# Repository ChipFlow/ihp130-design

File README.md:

# GF130 Test Chip Repo

## VS Code debugger

* Download the [latest VSIX package](https://github.com/ChipFlow/rtl-debugger/releases/tag/latest) for the extension.
* Install it (eg `code --install-extension ../rtl-debugger-0.0.0.vsix` or right-click in explorer pane and select "Install VSIX").
* `Shift+Ctrl+P` "RTL Debugger: Start Session"
* `Shift+Ctrl+P` "RTL Debugger: Run Simulation Until..." "10ms"
* `Shift+Ctrl+P` "RTL Debugger: Go to Time..." "10ms"

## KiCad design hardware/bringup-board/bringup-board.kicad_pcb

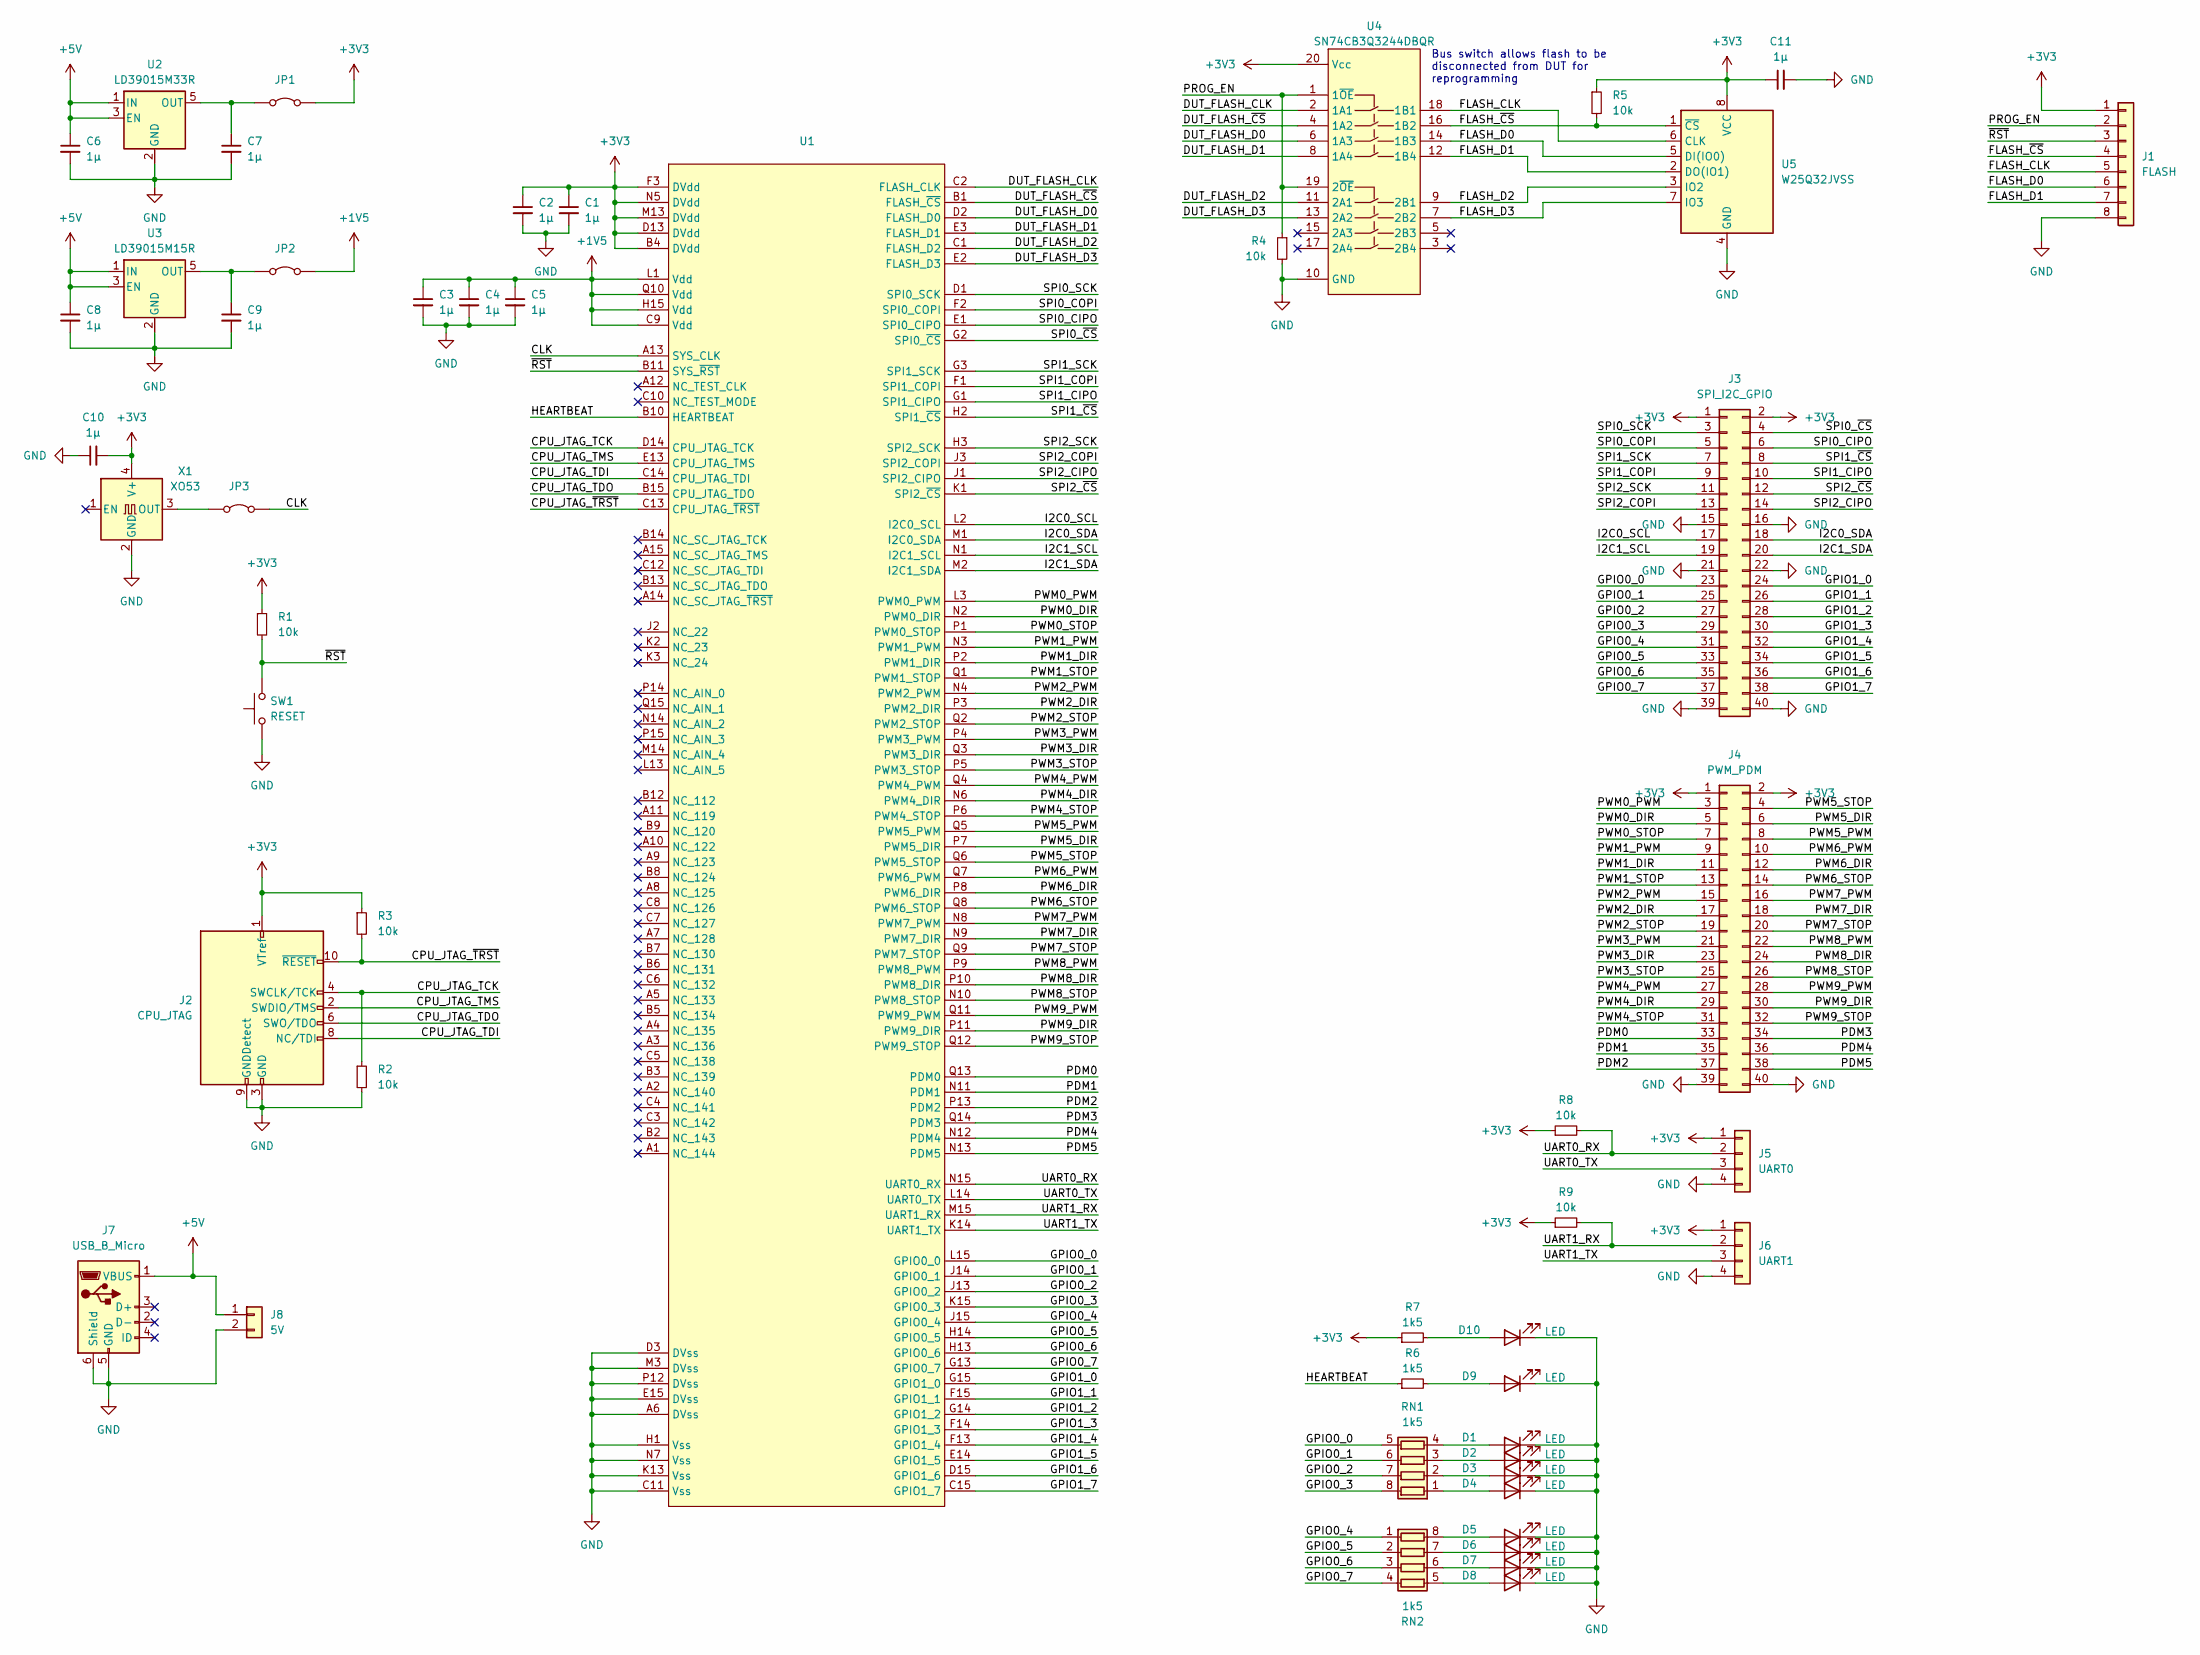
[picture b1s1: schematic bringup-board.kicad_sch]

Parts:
C1, C2, C3, C4, C5, C6, C7, C8, C9, C10, C11: 1µ; C_0603_1608Metric
D1, D2, D3, D4, D5, D6, D7, D8, D9, D10: LED; LED_0805_2012Metric
J1: FLASH; PinHeader_1x08_P2.54mm_Vertical
J2: CPU_JTAG; IDC-Header_2x05_P2.54mm_Vertical
J3: SPI_I2C_GPIO; PinHeader_2x20_P2.54mm_Vertical
J4: PWM_PDM; PinHeader_2x20_P2.54mm_Vertical
J5: UART0; PinHeader_1x04_P2.54mm_Vertical
J6: UART1; PinHeader_1x04_P2.54mm_Vertical
J7: USB_B_Micro; USB_Micro-B_Molex-105017-0001
J8: 5V; PinHeader_1x02_P2.54mm_Vertical
JP1, JP2, JP3: PinHeader_1x02_P2.54mm_Vertical
R1, R2, R3, R4, R5, R8, R9: 10k; R_0603_1608Metric
R6, R7: 1k5; R_0603_1608Metric
RN1, RN2: 1k5; R_Array_Convex_4x0402
SW1: RESET; SW_SPST_B3S-1000
U1: 145-PRS15024-12
U2: LD39015M33R; SOT-23-5
U3: LD39015M15R; SOT-23-5
U4: SN74CB3Q3244DBQR; SSOP-20_3.9x8.7mm_P0.635mm
U5: W25Q32JVSS; SOIC-8_5.23x5.23mm_P1.27mm
X1: XO53; Oscillator_SMD_EuroQuartz_XO53-4Pin_5.0x3.2mm

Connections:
+1V5: C3.1, C4.1, C5.1, JP2.2 (B), U1.C9 (Vdd), U1.H15 (Vdd), U1.L1 (Vdd), U1.Q10 (Vdd)
+3V3: C1.1, C2.1, C10.2, C11.1, J1.1, J2.1 (VTref), J3.1, J3.2, J4.1, J4.2, J5.1, J6.1, JP1.2 (B), R1.1, R3.1, R5.1, R7.1, R8.1, R9.1, U1.B4 (DVdd), U1.D13 (DVdd), U1.F3 (DVdd), U1.M13 (DVdd), U1.N5 (DVdd), U4.20 (Vcc), U5.8 (VCC), X1.4 (V+)
+5V: C6.1, C8.1, J7.1 (VBUS), J8.1, U2.1 (IN), U2.3 (EN), U3.1 (IN), U3.3 (EN)
/CLK: JP3.2 (B), U1.A13 (SYS_CLK)
/CPU_JTAG_TCK: J2.4 (SWCLK/TCK), R2.1, U1.D14 (CPU_JTAG_TCK)
/CPU_JTAG_TDI: J2.8 (NC/TDI), U1.C14 (CPU_JTAG_TDI)
/CPU_JTAG_TDO: J2.6 (SWO/TDO), U1.B15 (CPU_JTAG_TDO)
/CPU_JTAG_TMS: J2.2 (SWDIO/TMS), U1.E13 (CPU_JTAG_TMS)
/CPU_JTAG_~TRST: J2.10 (~RESET), R3.2, U1.C13 (CPU_JTAG_~TRST)
/DUT_FLASH_CLK: U1.C2 (FLASH_CLK), U4.2 (1A1)
/DUT_FLASH_D0: U1.D2 (FLASH_D0), U4.6 (1A3)
/DUT_FLASH_D1: U1.E3 (FLASH_D1), U4.8 (1A4)
/DUT_FLASH_D2: U1.C1 (FLASH_D2), U4.11 (2A1)
/DUT_FLASH_D3: U1.E2 (FLASH_D3), U4.13 (2A2)
/DUT_FLASH_~CS: U1.B1 (FLASH_~CS), U4.4 (1A2)
/FLASH_CLK: J1.5, U4.18 (1B1), U5.6 (CLK)
/FLASH_D0: J1.6, U4.14 (1B3), U5.5 (DI(IO0))
/FLASH_D1: J1.7, U4.12 (1B4), U5.2 (DO(IO1))
/FLASH_D2: U4.9 (2B1), U5.3 (IO2)
/FLASH_D3: U4.7 (2B2), U5.7 (IO3)
/FLASH_~CS: J1.4, R5.2, U4.16 (1B2), U5.1 (~CS)
/GPIO0_0: J3.23, RN1.5 (R4.2), U1.L15 (GPIO0_0)
/GPIO0_1: J3.25, RN1.6 (R3.2), U1.J14 (GPIO0_1)
/GPIO0_2: J3.27, RN1.7 (R2.2), U1.J13 (GPIO0_2)
/GPIO0_3: J3.29, RN1.8 (R1.2), U1.K15 (GPIO0_3)
/GPIO0_4: J3.31, RN2.1 (R1.1), U1.J15 (GPIO0_4)
/GPIO0_5: J3.33, RN2.2 (R2.1), U1.H14 (GPIO0_5)
/GPIO0_6: J3.35, RN2.3 (R3.1), U1.H13 (GPIO0_6)
/GPIO0_7: J3.37, RN2.4 (R4.1), U1.G13 (GPIO0_7)
/GPIO1_0: J3.24, U1.G15 (GPIO1_0)
/GPIO1_1: J3.26, U1.F15 (GPIO1_1)
/GPIO1_2: J3.28, U1.G14 (GPIO1_2)
/GPIO1_3: J3.30, U1.F14 (GPIO1_3)
/GPIO1_4: J3.32, U1.F13 (GPIO1_4)
/GPIO1_5: J3.34, U1.E14 (GPIO1_5)
/GPIO1_6: J3.36, U1.D15 (GPIO1_6)
/GPIO1_7: J3.38, U1.C15 (GPIO1_7)
/HEARTBEAT: R6.1, U1.B10 (HEARTBEAT)
/I2C0_SCL: J3.17, U1.L2 (I2C0_SCL)
/I2C0_SDA: J3.18, U1.M1 (I2C0_SDA)
/I2C1_SCL: J3.19, U1.N1 (I2C1_SCL)
/I2C1_SDA: J3.20, U1.M2 (I2C1_SDA)
/PDM0: J4.33, U1.Q13 (PDM0)
/PDM1: J4.35, U1.N11 (PDM1)
/PDM2: J4.37, U1.P13 (PDM2)
/PDM3: J4.34, U1.Q14 (PDM3)
/PDM4: J4.36, U1.N12 (PDM4)
/PDM5: J4.38, U1.N13 (PDM5)
/PROG_EN: J1.2, R4.1, U4.1 (1~OE), U4.19 (2~OE)
/PWM0_DIR: J4.5, U1.N2 (PWM0_DIR)
/PWM0_PWM: J4.3, U1.L3 (PWM0_PWM)
/PWM0_STOP: J4.7, U1.P1 (PWM0_STOP)
/PWM1_DIR: J4.11, U1.P2 (PWM1_DIR)
/PWM1_PWM: J4.9, U1.N3 (PWM1_PWM)
/PWM1_STOP: J4.13, U1.Q1 (PWM1_STOP)
/PWM2_DIR: J4.17, U1.P3 (PWM2_DIR)
/PWM2_PWM: J4.15, U1.N4 (PWM2_PWM)
/PWM2_STOP: J4.19, U1.Q2 (PWM2_STOP)
/PWM3_DIR: J4.23, U1.Q3 (PWM3_DIR)
/PWM3_PWM: J4.21, U1.P4 (PWM3_PWM)
/PWM3_STOP: J4.25, U1.P5 (PWM3_STOP)
/PWM4_DIR: J4.29, U1.N6 (PWM4_DIR)
/PWM4_PWM: J4.27, U1.Q4 (PWM4_PWM)
/PWM4_STOP: J4.31, U1.P6 (PWM4_STOP)
/PWM5_DIR: J4.6, U1.P7 (PWM5_DIR)
/PWM5_PWM: J4.8, U1.Q5 (PWM5_PWM)
/PWM5_STOP: J4.4, U1.Q6 (PWM5_STOP)
/PWM6_DIR: J4.12, U1.P8 (PWM6_DIR)
/PWM6_PWM: J4.10, U1.Q7 (PWM6_PWM)
/PWM6_STOP: J4.14, U1.Q8 (PWM6_STOP)
/PWM7_DIR: J4.18, U1.N9 (PWM7_DIR)
/PWM7_PWM: J4.16, U1.N8 (PWM7_PWM)
/PWM7_STOP: J4.20, U1.Q9 (PWM7_STOP)
/PWM8_DIR: J4.24, U1.P10 (PWM8_DIR)
/PWM8_PWM: J4.22, U1.P9 (PWM8_PWM)
/PWM8_STOP: J4.26, U1.N10 (PWM8_STOP)
/PWM9_DIR: J4.30, U1.P11 (PWM9_DIR)
/PWM9_PWM: J4.28, U1.Q11 (PWM9_PWM)
/PWM9_STOP: J4.32, U1.Q12 (PWM9_STOP)
/SPI0_CIPO: J3.6, U1.E1 (SPI0_CIPO)
/SPI0_COPI: J3.5, U1.F2 (SPI0_COPI)
/SPI0_SCK: J3.3, U1.D1 (SPI0_SCK)
/SPI0_~CS: J3.4, U1.G2 (SPI0_~CS)
/SPI1_CIPO: J3.10, U1.G1 (SPI1_CIPO)
/SPI1_COPI: J3.9, U1.F1 (SPI1_COPI)
/SPI1_SCK: J3.7, U1.G3 (SPI1_SCK)
/SPI1_~CS: J3.8, U1.H2 (SPI1_~CS)
/SPI2_CIPO: J3.14, U1.J1 (SPI2_CIPO)
/SPI2_COPI: J3.13, U1.J3 (SPI2_COPI)
/SPI2_SCK: J3.11, U1.H3 (SPI2_SCK)
/SPI2_~CS: J3.12, U1.K1 (SPI2_~CS)
/UART0_RX: J5.2, R8.2, U1.N15 (UART0_RX)
/UART0_TX: J5.3, U1.L14 (UART0_TX)
/UART1_RX: J6.2, R9.2, U1.M15 (UART1_RX)
/UART1_TX: J6.3, U1.K14 (UART1_TX)
/~RST: J1.3, R1.2, SW1.2, U1.B11 (SYS_~RST)
GND: C1.2, C2.2, C3.2, C4.2, C5.2, C6.2, C7.2, C8.2, C9.2, C10.1, C11.2, D1.1 (K), D2.1 (K), D3.1 (K), D4.1 (K), D5.1 (K), D6.1 (K), D7.1 (K), D8.1 (K), D9.1 (K), D10.1 (K), J1.8, J2.3 (GND), J2.5 (GND), J2.9 (GNDDetect), J3.15, J3.16, J3.21, J3.22, J3.39, J3.40, J4.39, J4.40, J5.4, J6.4, J7.5 (GND), J7.6 (Shield), J8.2, R2.2, R4.2, SW1.1, U1.A6 (DVss), U1.C11 (Vss), U1.D3 (DVss), U1.E15 (DVss), U1.H1 (Vss), U1.K13 (Vss), U1.M3 (DVss), U1.N7 (Vss), U1.P12 (DVss), U2.2 (GND), U3.2 (GND), U4.10 (GND), U5.4 (GND), X1.2 (GND)
unnamed: D1.2 (A), RN1.4 (R4.1)
unnamed: D2.2 (A), RN1.3 (R3.1)
unnamed: D3.2 (A), RN1.2 (R2.1)
unnamed: D4.2 (A), RN1.1 (R1.1)
unnamed: D5.2 (A), RN2.8 (R1.2)
unnamed: D6.2 (A), RN2.7 (R2.2)
unnamed: D7.2 (A), RN2.6 (R3.2)
unnamed: D8.2 (A), RN2.5 (R4.2)
unnamed: D9.2 (A), R6.2
unnamed: D10.2 (A), R7.2
unnamed: C7.1, JP1.1 (A), U2.5 (OUT)
unnamed: C9.1, JP2.1 (A), U3.5 (OUT)
unnamed: JP3.1 (A), X1.3 (OUT)

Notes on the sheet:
Bus switch allows flash to be disconnected from DUT for reprogramming

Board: 2 copper layers, 50 parts (3 on the bottom side), 110 nets, no tracks yet.

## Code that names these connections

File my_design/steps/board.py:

from amaranth_boards.ulx3s import ULX3S_85F_Platform

from chipflow_lib.steps.board import BoardStep

from amaranth import *
from amaranth.lib import wiring
from amaranth.lib.wiring import connect, flipped
from amaranth.build import Resource, Subsignal, Pins, Attrs

from ..design import MySoC

class BoardSocWrapper(wiring.Component):
    def __init__(self):
        super().__init__({})
    def elaborate(self, platform):
        m = Module()
        m.submodules.soc = soc = MySoC()

        m.domains += ClockDomain("sync")
        m.submodules.clock_reset_provider = platform.providers.ClockResetProvider()

        m.submodules.spiflash_provider = spiflash_provider = platform.providers.QSPIFlashProvider()
        connect(m, flipped(spiflash_provider.pins), soc.flash)

        m.submodules.led_gpio_provider = led_gpio_provider = platform.providers.LEDGPIOProvider()
        connect(m, flipped(led_gpio_provider.pins), soc.gpio_0)

        m.submodules.uart_provider = uart_provider = platform.providers.UARTProvider()
        connect(m, flipped(uart_provider.pins), soc.uart_0)

        # Extra IO on headers
        platform.add_resources([
            Resource(
                "expansion",
                0,
                Subsignal("user_spi0_sck",  Pins("0+", conn=("gpio", 0), dir='o')),
                Subsignal("user_spi0_copi", Pins("0-", conn=("gpio", 0), dir='o')),
                Subsignal("user_spi0_cipo", Pins("1+", conn=("gpio", 0), dir='i')),
                Subsignal("user_spi0_csn", Pins("1-", conn=("gpio", 0), dir='o')),

                Subsignal("user_spi1_sck",  Pins("2+", conn=("gpio", 0), dir='o')),
                Subsignal("user_spi1_copi", Pins("2-", conn=("gpio", 0), dir='o')),
                Subsignal("user_spi1_cipo", Pins("3+", conn=("gpio", 0), dir='i')),
                Subsignal("user_spi1_csn", Pins("3-", conn=("gpio", 0), dir='o')),

                Subsignal("i2c0_sda", Pins("4+", conn=("gpio", 0), dir='io')),
                Subsignal("i2c0_scl", Pins("4-", conn=("gpio", 0), dir='io')),

                Subsignal("motor_pwm0_pwm",  Pins("5+", conn=("gpio", 0), dir='o')),
                Subsignal("motor_pwm0_dir",  Pins("5-", conn=("gpio", 0), dir='o')),
                Subsignal("motor_pwm0_stop", Pins("6+", conn=("gpio", 0), dir='i'), Attrs(PULLMODE="DOWN")),

                Subsignal("motor_pwm1_pwm",  Pins("6-", conn=("gpio", 0), dir='o')),
                Subsignal("motor_pwm1_dir",  Pins("7+", conn=("gpio", 0), dir='o')),
                Subsignal("motor_pwm1_stop", Pins("7-", conn=("gpio", 0), dir='i'), Attrs(PULLMODE="DOWN")),

                Subsignal("uart1_rx", Pins("8+", conn=("gpio", 0), dir='i')),
                Subsignal("uart1_tx", Pins("8-", conn=("gpio", 0), dir='o')),

                Subsignal("cpu_jtag_tck", Pins("9+", conn=("gpio", 0), dir='i')),
                Subsignal("cpu_jtag_tms", Pins("9-", conn=("gpio", 0), dir='i')),
                Subsignal("cpu_jtag_tdi", Pins("10+", conn=("gpio", 0), dir='i')),
                Subsignal("cpu_jtag_tdo", Pins("10-", conn=("gpio", 0), dir='o')),
                Subsignal("cpu_jtag_trst", Pins("11+", conn=("gpio", 0), dir='i')),

                Attrs(IO_TYPE="LVCMOS33", PULLMODE="UP"),
            )
        ])

        exp = platform.request("expansion")
        def _connect_interface(interface, name):
            pins = dict()
            for member in interface.signature.members:
                pin, suffix = member.rsplit("_", 2)
                assert suffix in ("o", "i", "oe"), suffix
                pins[pin] = getattr(interface, member).width
            for pin, width in pins.items():
                for i in range(width):
                    platform_pin = getattr(exp, f"{name}_{pin}{'' if width == 1 else str(i)}")
                    if hasattr(interface, f"{pin}_i"):
                        m.d.comb += getattr(interface, f"{pin}_i")[i].eq(platform_pin.i)
                    if hasattr(interface, f"{pin}_o"):
                        m.d.comb += platform_pin.o.eq(getattr(interface, f"{pin}_o")[i])
                    if hasattr(interface, f"{pin}_oe"):
                        m.d.comb += platform_pin.oe.eq(getattr(interface, f"{pin}_oe")[i])

        _connect_interface(soc.user_spi_0, "user_spi0")
        _connect_interface(soc.user_spi_1, "user_spi1")

        _connect_interface(soc.i2c_0, "i2c0")

        _connect_interface(soc.motor_pwm0, "motor_pwm0")
        _connect_interface(soc.motor_pwm1, "motor_pwm1")

        _connect_interface(soc.uart_1, "uart1")

        _connect_interface(soc.cpu_jtag, "cpu_jtag")

        return m

class MyBoardStep(BoardStep):
    def __init__(self, config):

        platform = ULX3S_85F_Platform()
        platform.providers = board_ulx3s_providers

        super().__init__(config, platform)

    def build(self):
        my_design = BoardSocWrapper()

        self.platform.build(my_design, do_program=False)

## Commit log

2024-09-14 Initial design commit
2024-09-14 sim: simplify RTL debug server invocation.
    It's no longer necessary to have an extra layer of indirection, and
    the debugger can be started at any point, with the full recorded
    context available.
    The overhead of recording a spool is quite low (25% on this design;
    11.487s while recording, 9.248s without the agent used at all).
2024-09-14 Add support to generate input actions from JSON
2024-09-14 Adding SPI peripheral
2024-09-14 Adding top-level Verilog generation
2024-09-14 First write and read command without checking
2024-09-14 Add RTL debugger support.
2024-09-14 chipflow-lib change was merged
2024-09-14 First version with SPI driver
2024-09-14 Check in the lockfile.
2024-09-14 Adding pyuvm+verilator enviroment
2024-09-14 Add VS Code instructions to README.md
2024-09-14 env works
2024-09-14 Adding the complete top-level
2024-09-14 Reduce SRAM to 2kB for now
2024-09-14 Fix the JSON comparison and reference
2024-09-14 Move providers out of SoC design
2024-09-14 Adding UART transmit model
2024-09-14 Update for latest Yosys/chipflow-lib
2024-09-14 Fixing driver_bfm
2024-09-14 Updating the simulation to remove providers/blackboxes and add event log
2024-09-14 Adding a toplevel design
2024-09-14 Add sim and checking of event json to CI
2024-09-14 Add GitHub Actions CI.
2024-09-14 Update chipflow-lib and ziglang.
2024-09-14 sim: update CXXRTL version.
2024-09-14 Adding I2C peripheral
2024-09-14 sim: -Os→-O3.
    The speedup is substantial and the difference in compile time small.
2024-09-14 adding spi wrap
2024-09-14 First complete test
2024-09-14 renaming comment and delete log messages
2024-09-14 removing clk divider test
2024-09-14 Add pwm for motors (#18)
    * -Add pwm for 10 motors needed.
    -Add integration test for pwm
    * resume unintendedly deleted agent.
    * fix compilation error
    * revert main.cc to origin/main
2024-09-14 - Implement a single bit pdm. Include an integration test (#20)
    - Use output pins without pins interface
    - pdm outval can now be maximum 16 bits
    - modify header to replace din with outval
    - add unit test for pdm
2024-09-14 pyproject: update chipflow-lib.
2024-09-14 add pwm unit test (#22)
2024-09-14 Add standalone export of SPI peripheral (#19)
    * Add standalone export of SPI peripheral
    * Update dependencies
    ---------
2024-09-14 removing clk divider checkers
2024-09-14 Adding export of I2C and SPIMemIO (QSPI XIP) IP for Verification (#25)
    * export: Add SPIMemIO verilog export
    * export: Add I2C verilog export
    ---------
2024-09-14 Update to verilator v5.028 for build on mac
2024-09-14 steps.board: fix motor_pwm{0,1} connections.
2024-09-14 macOS simulation fixes (#26)
    * Update to newest yowasp-yosys with fixes (0.40.0.68.post721.dev0). Needs override because of chipflow-lib version.
    * Updated cxxrtl_server.h
2024-09-14 Add CI for MacOS 12,13,14, latest ubuntu and latest LTS, and python 3.9->3.12
2024-09-14 Add mac and ubuntu LTS to testset
2024-09-14 including sim_build../Makefile
2024-09-14 Fix of generation verilog modules
2024-09-14 Remove peripheral names as a result of RFC 70.
2024-09-14 steps.board: define sync clock domain at the top-level.
    See chipflow/chipflow-lib#10.
2024-09-14 adding instance of spi peripheral
2024-09-14 Use Amaranth SoC GPIO peripheral.
2024-09-14 Adding new tests for SPI (#27)
    * Adding new tests for SPI
    * Removing unused signal
2024-09-14 force C++ 20 for building verilator generated sources
2024-09-14 Disable pyuvm for now, as verilator builds fail on mac
2024-09-14 Add project_id for chipflow app
2024-11-07 Bump dependencies.
2024-11-07 Replace CV32E40P with Minerva.
2024-11-07 Replace SPI flash controller peripheral.
2024-11-07 Simulation improvements.
2024-11-07 Reduce SRAM size to 1kB.
2024-11-07 design: disable RV32M support to save area.
2024-11-07 Add Zephyr OS demo.
2024-11-07 Remove unused peripherals.
2024-11-07 Remove wrapper of obsolete SPI flash controller.
2024-11-07 sim: add workaround for CXXRTL agent.
2024-11-07 Fix for CXXRTL protocol deviation.
2024-11-07 board: swap uart rx/tx.
2024-11-07 spi_flash: remove dummy cycle.
2024-11-07 fix uart divisor for 48mhz clkfreq.
2024-11-07 update ci
2024-11-07 Run CI on all branches
2024-11-07 Bump versions and make CI work
2024-11-11 cleanup: Remove PyUVM based tests
2024-11-11 feat: Change to use the open IHP SG13G2 process
2024-11-11 chore: Fix dependencies
2024-11-13 chore: ihp_sg13g2 support now merged into chipflow-lib main
2024-11-19 IMEC workshop demo SoC.
2024-11-19 chipflow.toml: fix type of sys_clk pad.
2024-11-19 chipflow.toml: remove unconnected pads.
2024-11-20 Support building sim on Windows
2024-11-21 steps/board: use GlasgowBuildPlan to build the bitstream.
2024-11-22 pyproject: Fetch toolchain with glasgow
2024-11-22 Add rules for ruff and pycodestyle suitable for Amaranth
2024-11-22 ci: Update for removal of makefile
2024-11-22 cf: Bump project ID to 13
2024-11-22 ci: Enable submit flow
2024-11-22 ci: run on push just for main
2024-11-25 Test
2024-11-25 andrews-test-branch
2024-11-25 all branches
2024-11-26 wip: add some tests
2024-12-19 empty
2025-01-14 toml port ideas
2025-01-14 New ChipFlow top structure
2025-01-14 more amaranthy
2025-02-03 Make a very tiny minimal soc
2025-02-03 make tinier?
2025-03-17 Chipflow-lib dep now merged
2025-03-17 Remove pyuvm tests
2025-03-17 Add pins.lock
2025-03-17 Run submit in CI
2025-03-17 Fix up software generation for latest amaranth-soc
2025-03-17 Send design to ChipFlow app (#28)
    * Send design to ChipFlow API
    * Updated sys_clk pad to be clock input
    ---------
2025-03-17 Use PinSignature for all port wiring
2025-03-17 chore: fix tests
2025-03-17 sim: use read_rtlil rather than read_ilang
2025-03-17 Fix up tests
2025-03-17 Use old backend api for now
2025-03-17 Fix to do everything modern CSR way
2025-03-17 chore: Fix for latest pdm and working on mac
2025-03-17 fix simulation
2025-03-17 No more passing pins for amaranth-orchard
2025-03-17 All signals going towards padring shoule be Out()
2025-03-17 Test submit dry run in ci
2025-03-17 chore: bump pytest req to >=7.3.1 for TestCaseFunction.addDuration support, lock latest amaranth-orchard
2025-03-17 chore: locking
2025-03-17 replaced gf130bcd with ihp_sg13g2
2025-03-17 Use port-wiring fix in chipflow-lib
2025-03-17 Update pyproject to use mainline chipflow-lib
2025-03-17 Fix workflow for main
2025-03-17 Rename SPI miso/mosi to more modern cipo/copi
2025-03-17 Remove pdm.lock and pins.lock, and lock in CI
2025-03-17 Remove old silicon.py/silicon2.py
2025-03-17 Update reference events for sim check
2025-03-17 Lower python version and use direct_minimal_versions locking strategy
2025-03-17 Update pyproject to point to main for amaranth-orchard and amaranth-cv32e40p
2025-03-17 Completely remove pyuvm
2025-03-17 Replace UART with that from amaranth-soc RFC
2025-03-17 push latest updates
2025-03-17 pcb: Add symbol with PGA144 pinout
2025-03-17 pcb: First cut schematic
2025-03-17 outline pcb placement
2025-03-18 README: remove outdated link
2025-03-18 Move I2C/SPI IP and driver out of repo
2025-03-20 Replace SPIMemIO with new QSPI core
2025-03-20 Bump vendored cxxrtl_server
